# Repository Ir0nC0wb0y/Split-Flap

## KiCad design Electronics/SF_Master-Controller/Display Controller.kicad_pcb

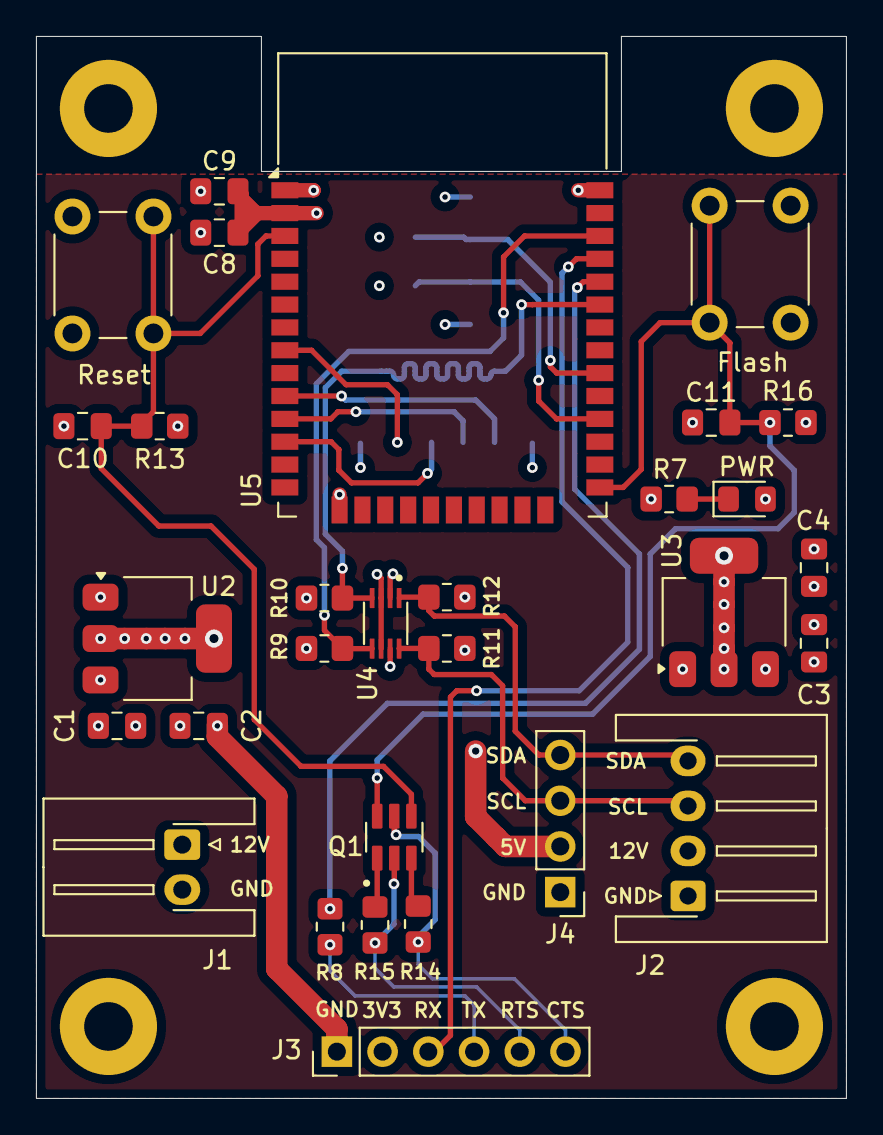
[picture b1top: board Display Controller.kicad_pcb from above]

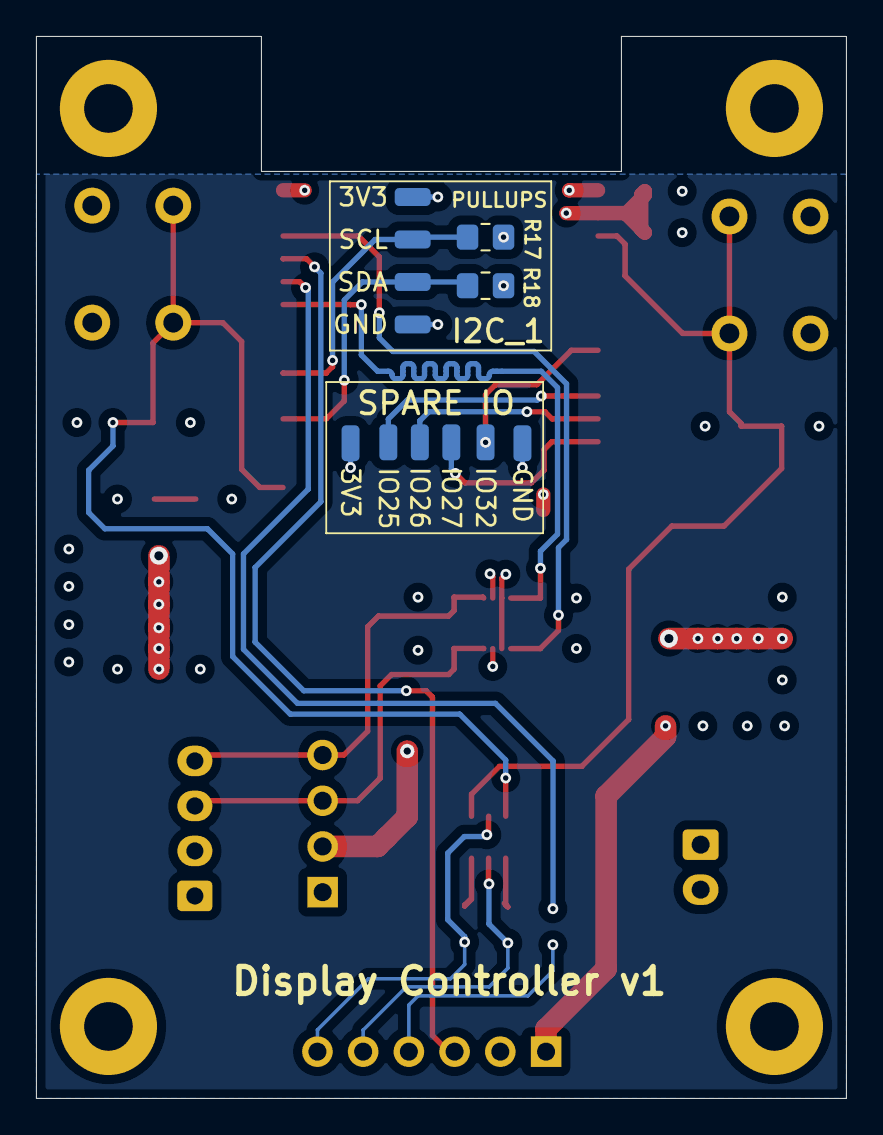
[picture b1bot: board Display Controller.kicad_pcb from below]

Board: 4 copper layers, 45.0 x 59.0 mm, 46 parts (12 on the bottom side), 24 nets.

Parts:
C1, C2, C3, C4: C; C_0805_2012Metric_Pad1.18x1.45mm_HandSolder
C8: 10uF; C_0805_2012Metric_Pad1.18x1.45mm_HandSolder
C9, C10, C11: 0.1uF; C_0805_2012Metric_Pad1.18x1.45mm_HandSolder
D1: LED; LED_0805_2012Metric_Pad1.15x1.40mm_HandSolder
H1, H2, H3, H4: MountingHole_Pad; MountingHole_2.7mm_M2.5_Pad
J1: Conn_01x02_Pin; JST_XH_S2B-XH-A-1_1x02_P2.50mm_Horizontal
J2: Conn_01x04_Pin; JST_XH_S4B-XH-A-1_1x04_P2.50mm_Horizontal
J3: Conn_01x06_Pin; PinHeader_1x06_P2.54mm_Vertical
J4: Conn_01x04_Pin; PinHeader_1x04_P2.54mm_Vertical
Q1: FMB2222A; SOT95P280X110-6N
R7: 150R; R_0805_2012Metric_Pad1.20x1.40mm_HandSolder
R8: 1k; R_0805_2012Metric_Pad1.20x1.40mm_HandSolder
R9, R10, R11, R12, R13, R14, R15, R16, R17, R18: 10k; R_0805_2012Metric_Pad1.20x1.40mm_HandSolder
SW3, SW4: SW_SPST; SW_PUSH_6mm_H4.3mm
TP1, TP2, TP3, TP4, TP5, TP6, TP7, TP8, TP9, TP10: TestPoint_Small; SolderWirePad_1x01_SMD_1x2mm
U2: LD1117S33TR_SOT223; SOT-223-3_TabPin2
U3: LD1117S50TR_SOT223; SOT-223-3_TabPin2
U4: TCA9406DCUR; SOP50P310X90-8N
U5: ESP32-WROOM-32E; ESP32-WROOM-32D

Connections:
+3V3: C2.1, C8.2, C9.2, J3.1, R9.1, R10.1, R13.1, R16.1, R17.1, R18.1, TP1.1, TP5.1, U2.2 (VO), U4.3 (VCCA), U4.6 (OE), U5.2 (VDD)
+5V: C4.1, D1.2 (A), J4.2, R11.1, R12.1, U3.2 (VO), U4.7 (VCCB)
+12V: C1.2, C3.2, J1.1, J2.2, U2.3 (VI), U3.3 (VI)
/ESP32/EN: C10.2, Q1.4, R13.2, SW3.2 (B), U5.3 (EN)
/ESP32/I2C_SCL_SPARE: R17.2, TP2.1, U5.30 (IO18)
/ESP32/I2C_SDA_SPARE: R18.2, TP3.1, U5.28 (IO17)
/ESP32/IO0: C11.2, Q1.6, R16.2, SW4.1 (A), U5.25 (IO0)
/ESP32/IO25: TP6.1, U5.10 (IO25)
/ESP32/IO26: TP7.1, U5.11 (IO26)
/ESP32/IO27: TP9.1, U5.12 (IO27)
/ESP32/IO32: TP10.1, U5.8 (IO32)
/I2C_SCL_5V: J2.3, J4.3, R11.2, U4.8 (SCL_B)
/I2C_SDA_5V: J2.4, J4.4, R12.2, U4.1 (SDA_B)
FTDI_CTS: J3.6, Q1.5, R14.1
FTDI_RTS: J3.5, Q1.2, R15.2
FTDI_RX: J3.3, U5.35 (TXD0/IO1)
FTDI_TX: R8.2, U5.34 (RXD0/IO3)
GND: C1.1, C2.2, C3.1, C4.2, C8.1, C9.1, C10.1, C11.1, J1.2, J2.1, J3.2, J4.1, R7.2, SW3.1 (A), SW4.2 (B), TP4.1, TP8.1, U2.1 (GND), U3.1 (GND), U4.2 (GND), U5.1 (GND), U5.15 (GND), U5.38 (GND)
I2C_SCL_3V3: R9.2, U4.5 (SCL_A), U5.36 (IO22)
I2C_SDA_3V3: R10.2, U4.4 (SDA_A), U5.33 (IO21)
unnamed: D1.1 (K), R7.1
unnamed: J3.4, R8.1
unnamed: Q1.1, R15.1
unnamed: Q1.3, R14.2

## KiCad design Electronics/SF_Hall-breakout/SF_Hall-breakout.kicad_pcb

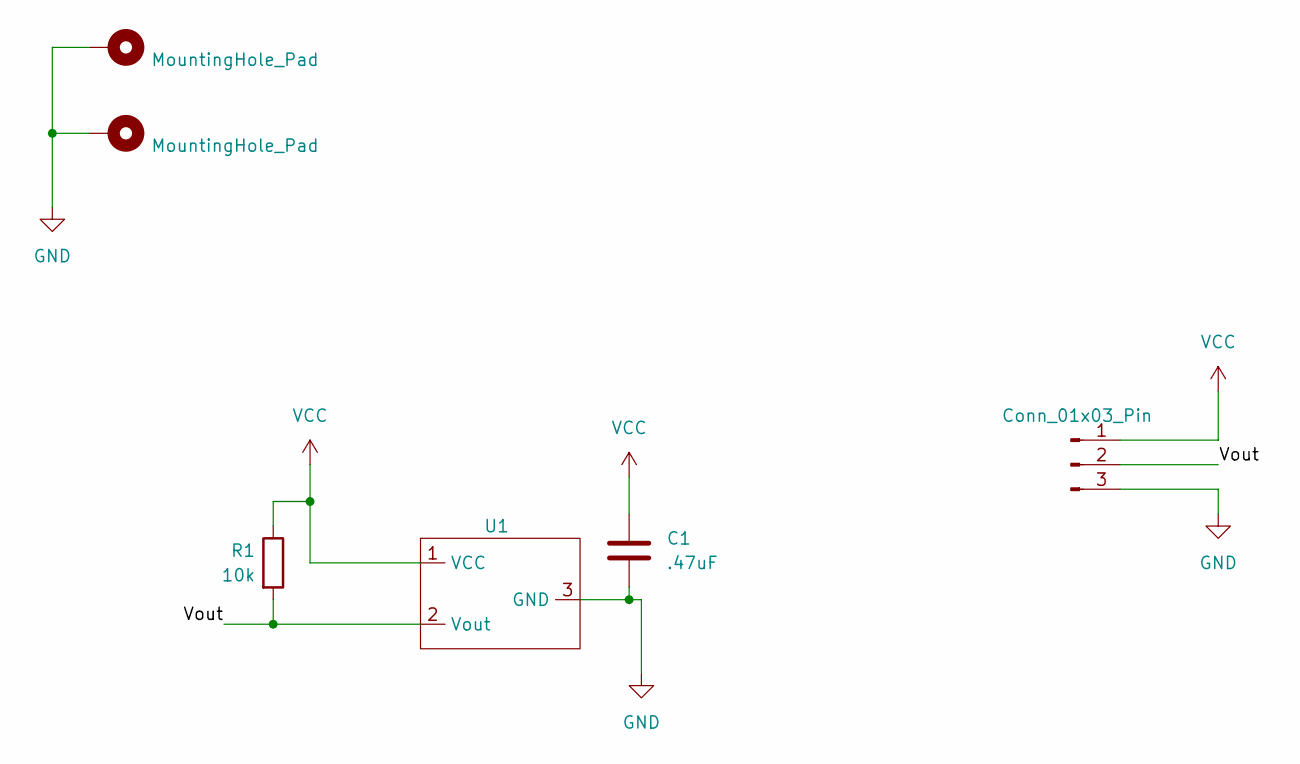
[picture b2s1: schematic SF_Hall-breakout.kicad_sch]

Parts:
C1: .47uF; C_0805_2012Metric_Pad1.18x1.45mm_HandSolder
H1, H2: MountingHole_Pad; MountingHole_2.2mm_M2_Pad
J1: Conn_01x03_Pin; PinHeader_1x03_P2.00mm_Vertical
R1: 10k; R_0805_2012Metric_Pad1.20x1.40mm_HandSolder
U1: SOT-23_Handsoldering

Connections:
/Vout: J1.2, R1.2, U1.2 (Vout)
GND: C1.2, H1.1, H2.1, J1.3, U1.3 (GND)
VCC: C1.1, J1.1, R1.1, U1.1 (VCC)

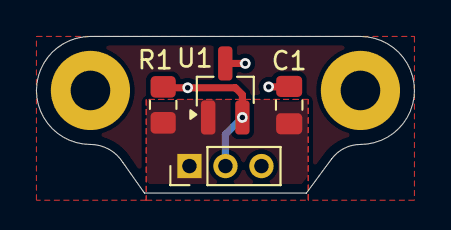
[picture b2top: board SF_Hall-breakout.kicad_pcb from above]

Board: 2 copper layers, 21.0 x 8.7 mm, 6 parts (0 on the bottom side), 3 nets.

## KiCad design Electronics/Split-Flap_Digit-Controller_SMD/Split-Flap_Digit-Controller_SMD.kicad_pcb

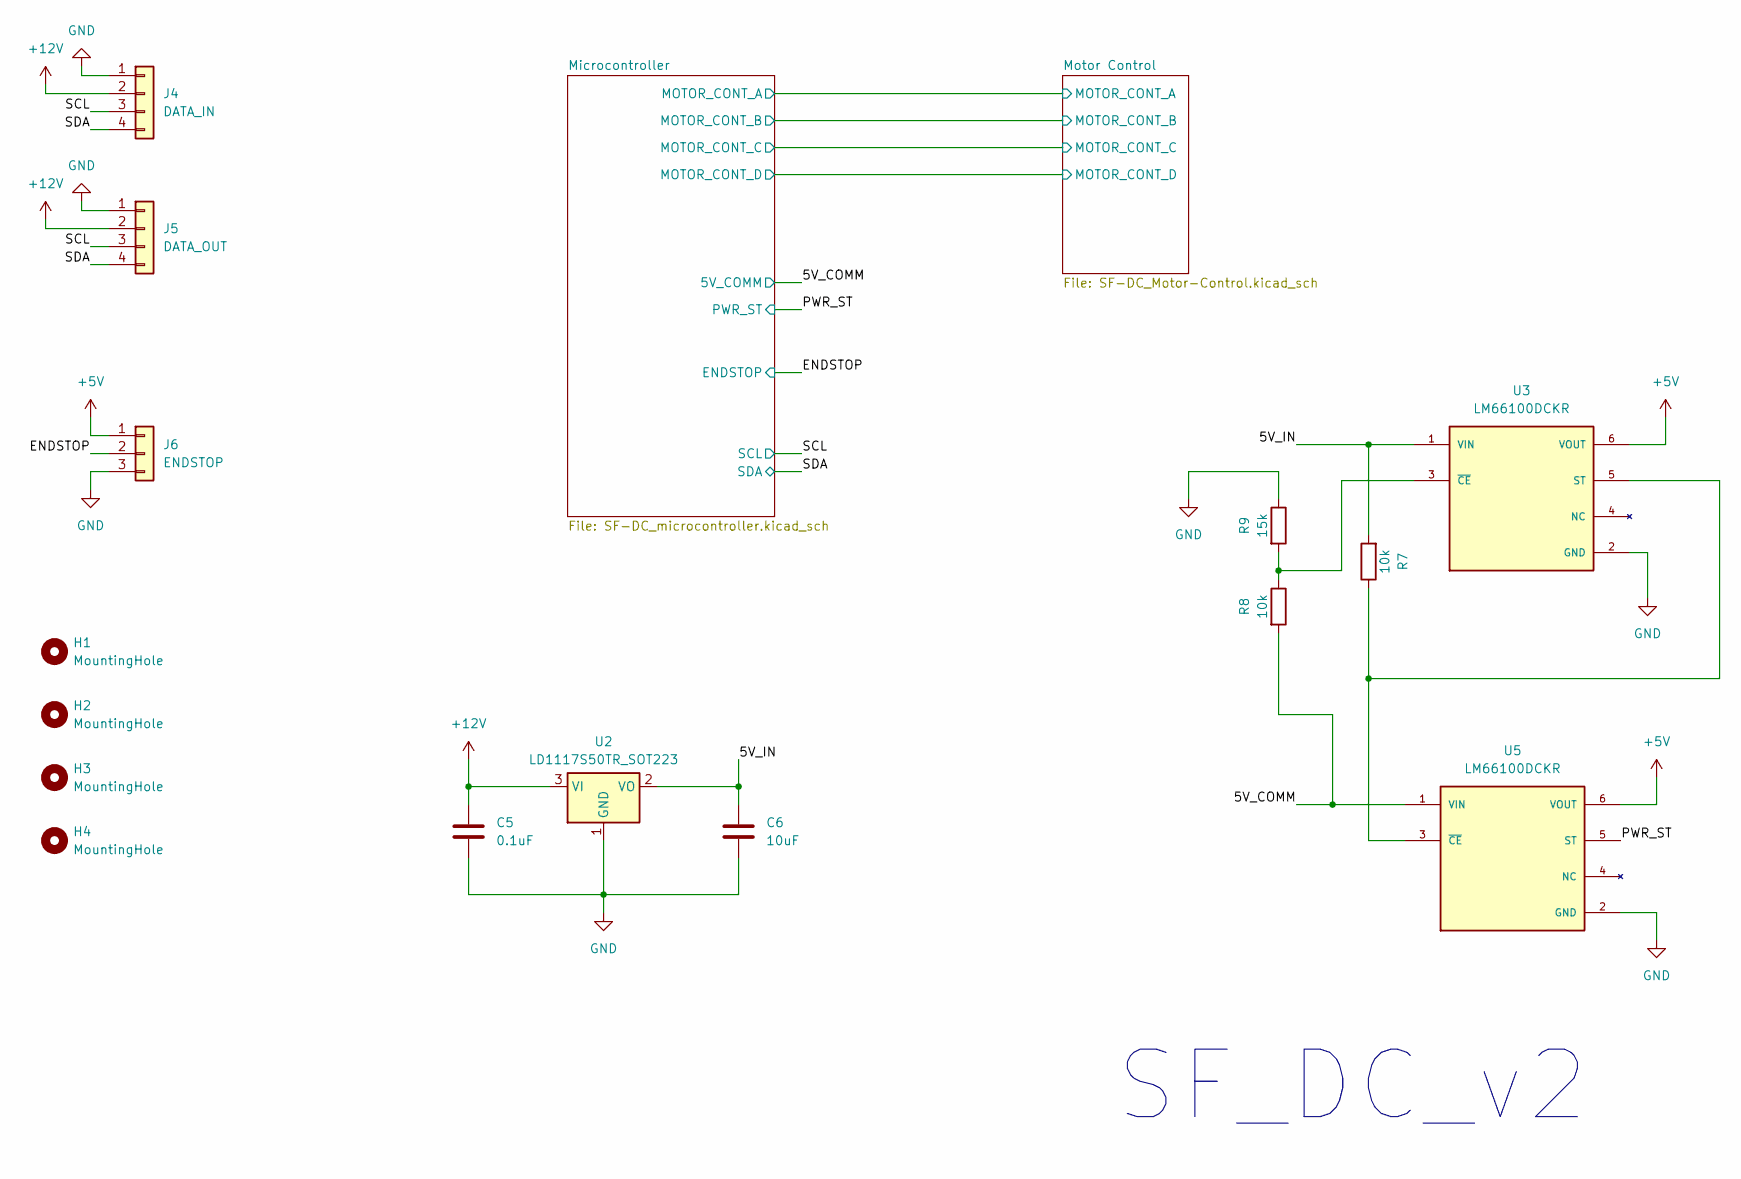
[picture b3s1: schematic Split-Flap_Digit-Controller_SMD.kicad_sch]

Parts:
C5: 0.1uF; LED_0805_2012Metric_Pad1.15x1.40mm_HandSolder
C6: 10uF; LED_0805_2012Metric_Pad1.15x1.40mm_HandSolder
H1, H2, H3, H4: MountingHole; MountingHole_2.7mm_M2.5_DIN965_Pad_TopBottom
J4: DATA_IN; JST_XH_S4B-XH-A-1_1x04_P2.50mm_Horizontal
J5: DATA_OUT; JST_XH_S4B-XH-A-1_1x04_P2.50mm_Horizontal
J6: ENDSTOP; JST_XH_S3B-XH-A-1_1x03_P2.50mm_Horizontal
R7, R8: 10k; R_0805_2012Metric_Pad1.20x1.40mm_HandSolder
R9: 15k; R_0805_2012Metric_Pad1.20x1.40mm_HandSolder
U2: LD1117S50TR_SOT223; SOT-223-3_TabPin2
U3, U5: LM66100DCKR; SOT65P210X110-6N; PARTREV Rev. A

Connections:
+5V: J6.1, U3.6 (VOUT), U5.6 (VOUT); also elsewhere on the board
+12V: C5.1, J4.2, J5.2, U2.3 (VI); also elsewhere on the board
/5V_COMM: R8.2, U5.1 (VIN); also elsewhere on the board
/5V_IN: C6.1, R7.2, U2.2 (VO), U3.1 (VIN)
/ENDSTOP: J6.2; also elsewhere on the board
/PWR_ST: U5.5 (ST); also elsewhere on the board
/SCL: J4.3, J5.3; also elsewhere on the board
/SDA: J4.4, J5.4; also elsewhere on the board
GND: C5.2, C6.2, J4.1, J5.1, J6.3, R9.1, U2.1 (GND), U3.2 (GND), U5.2 (GND); also elsewhere on the board
unnamed: R7.1, U3.5 (ST), U5.3 (~CE)
unnamed: R8.1, R9.2, U3.3 (~CE)

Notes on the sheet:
SF_DC_v2

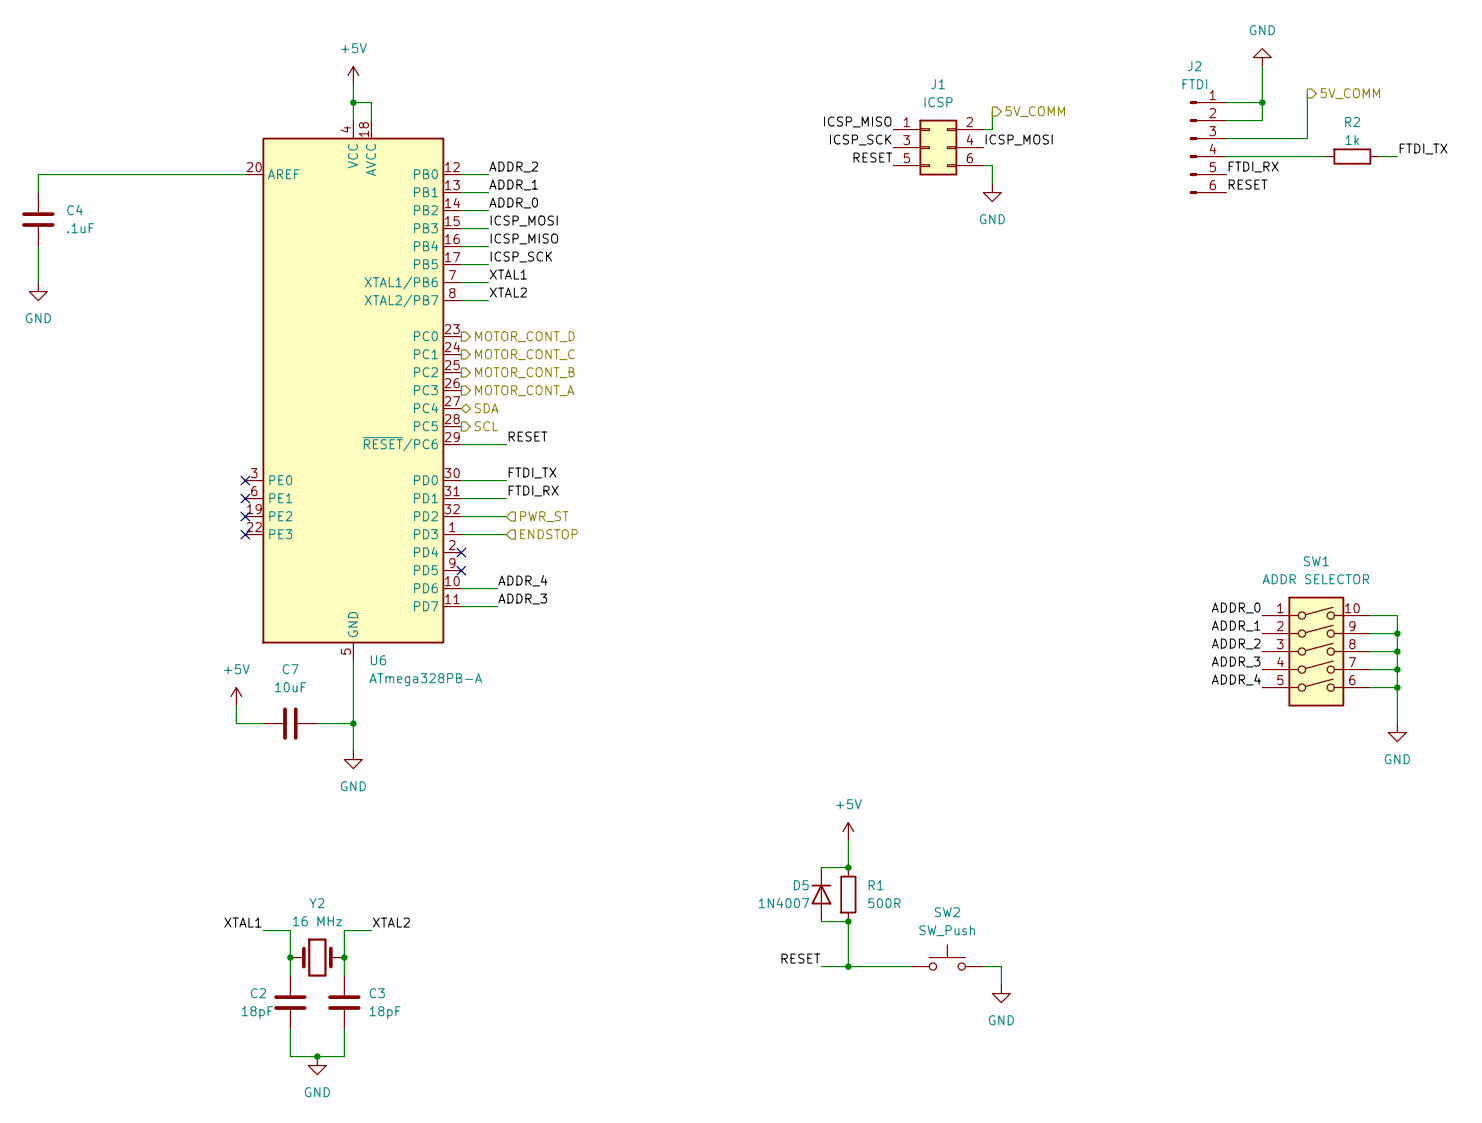
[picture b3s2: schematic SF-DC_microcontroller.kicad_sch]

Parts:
C2: 18pF; C_0805_2012Metric_Pad1.18x1.45mm_HandSolder; Part Number FG28C0G1H180JNT06
C3: 18pF; C_0805_2012Metric_Pad1.18x1.45mm_HandSolder; part_no FG28C0G1H180JNT06
C4: .1uF; C_0805_2012Metric_Pad1.18x1.45mm_HandSolder
C7: 10uF; C_0805_2012Metric_Pad1.18x1.45mm_HandSolder
D5: 1N4007; D_SMA_Handsoldering
J1: ICSP; PinHeader_2x03_P2.54mm_Vertical
J2: FTDI; PinHeader_1x06_P2.54mm_Vertical
R1: 500R; R_0805_2012Metric_Pad1.20x1.40mm_HandSolder
R2: 1k; R_0805_2012Metric_Pad1.20x1.40mm_HandSolder
SW1: ADDR SELECTOR; SW_DIP_SPSTx05_Slide_6.7x14.26mm_W7.62mm_P2.54mm_LowProfile
SW2: SW_Push; SW_PUSH_6mm
U6: ATmega328PB-A; TQFP-32_7x7mm_P0.8mm
Y2: 16 MHz; Crystal_SMD_0603-2Pin_6.0x3.5mm_HandSoldering

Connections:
+5V: C7.2, D5.1 (K), R1.1, U6.4 (VCC), U6.18 (AVCC); also elsewhere on the board
/5V_COMM: J1.2, J2.3; also elsewhere on the board
/ENDSTOP: U6.1 (PD3); also elsewhere on the board
/Microcontroller/ADDR_0: SW1.1, U6.14 (PB2)
/Microcontroller/ADDR_1: SW1.2, U6.13 (PB1)
/Microcontroller/ADDR_2: SW1.3, U6.12 (PB0)
/Microcontroller/ADDR_3: SW1.4, U6.11 (PD7)
/Microcontroller/ADDR_4: SW1.5, U6.10 (PD6)
/Microcontroller/FTDI_RX: J2.5, U6.31 (PD1)
/Microcontroller/FTDI_TX: R2.1, U6.30 (PD0)
/Microcontroller/ICSP_MISO: J1.1, U6.16 (PB4)
/Microcontroller/ICSP_MOSI: J1.4, U6.15 (PB3)
/Microcontroller/ICSP_SCK: J1.3, U6.17 (PB5)
/Microcontroller/MOTOR_CONT_A: U6.26 (PC3); also elsewhere on the board
/Microcontroller/MOTOR_CONT_B: U6.25 (PC2); also elsewhere on the board
/Microcontroller/MOTOR_CONT_C: U6.24 (PC1); also elsewhere on the board
/Microcontroller/MOTOR_CONT_D: U6.23 (PC0); also elsewhere on the board
/Microcontroller/RESET: D5.2 (A), J1.5, J2.6, R1.2, SW2.1, U6.29 (~RESET/PC6)
/Microcontroller/XTAL1: C2.2, U6.7 (XTAL1/PB6), Y2.1
/Microcontroller/XTAL2: C3.2, U6.8 (XTAL2/PB7), Y2.2
/PWR_ST: U6.32 (PD2); also elsewhere on the board
/SCL: U6.28 (PC5); also elsewhere on the board
/SDA: U6.27 (PC4); also elsewhere on the board
GND: C2.1, C3.1, C4.2, C7.1, J1.6, J2.1, J2.2, SW1.6, SW1.7, SW1.8, SW1.9, SW1.10, SW2.2, U6.5 (GND), U6.21 (GND); also elsewhere on the board
unnamed: J2.4, R2.2
unnamed: C4.1, U6.20 (AREF)

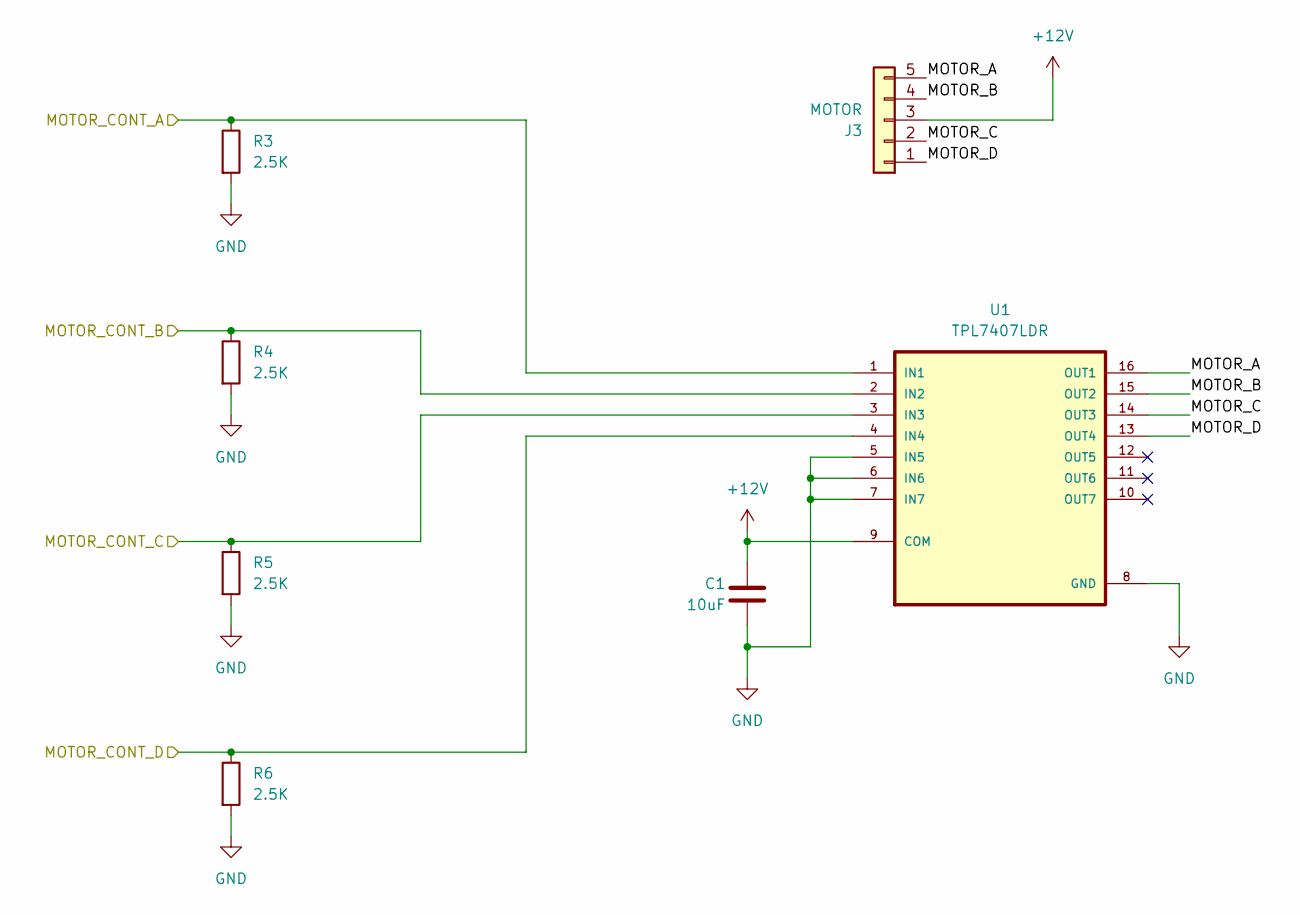
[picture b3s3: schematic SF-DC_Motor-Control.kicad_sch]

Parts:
C1: 10uF; R_0805_2012Metric_Pad1.20x1.40mm_HandSolder
J3: MOTOR; JST_XH_S5B-XH-A-1_1x05_P2.50mm_Horizontal
R3, R4, R5, R6: 2.5K; R_0805_2012Metric_Pad1.20x1.40mm_HandSolder
U1: TPL7407LDR; SOIC127P600X175-16N

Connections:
+12V: C1.2, J3.3, U1.9 (COM); also elsewhere on the board
/Microcontroller/MOTOR_CONT_A: R3.1, U1.1 (IN1); also elsewhere on the board
/Microcontroller/MOTOR_CONT_B: R4.1, U1.2 (IN2); also elsewhere on the board
/Microcontroller/MOTOR_CONT_C: R5.1, U1.3 (IN3); also elsewhere on the board
/Microcontroller/MOTOR_CONT_D: R6.1, U1.4 (IN4); also elsewhere on the board
/Motor Control/MOTOR_A: J3.5, U1.16 (OUT1)
/Motor Control/MOTOR_B: J3.4, U1.15 (OUT2)
/Motor Control/MOTOR_C: J3.2, U1.14 (OUT3)
/Motor Control/MOTOR_D: J3.1, U1.13 (OUT4)
GND: C1.1, R3.2, R4.2, R5.2, R6.2, U1.5 (IN5), U1.6 (IN6), U1.7 (IN7), U1.8 (GND); also elsewhere on the board

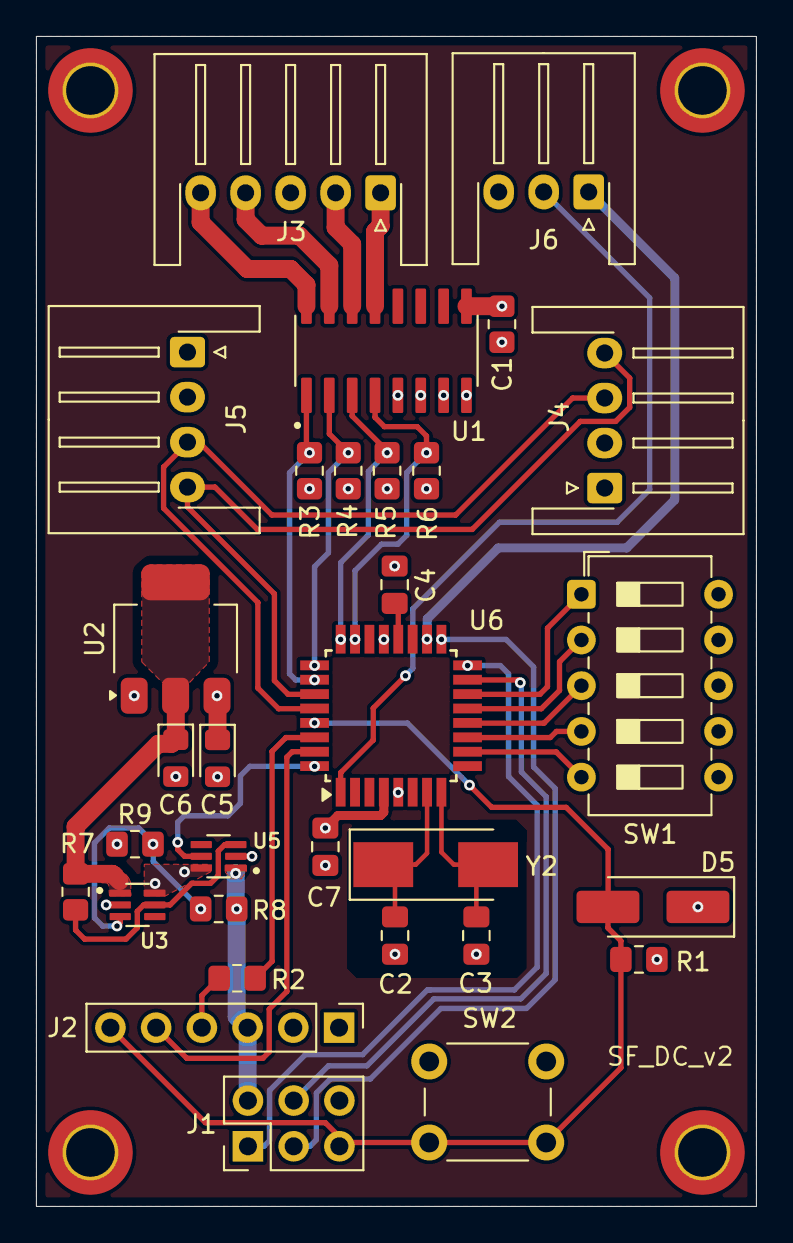
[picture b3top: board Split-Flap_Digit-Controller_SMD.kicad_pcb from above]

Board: 4 copper layers, 40.0 x 65.0 mm, 35 parts (0 on the bottom side), 34 nets.

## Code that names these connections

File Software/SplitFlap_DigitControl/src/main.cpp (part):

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// Stepper lib expects: blue-yellow, pink-orange


#define PIN_MOTOR_A 17  // yellow
#define PIN_MOTOR_B 16  // orange
#define PIN_MOTOR_C 15  // pink
#define PIN_MOTOR_D 14  // blue
#define PIN_ENDSTOP  3
#define PIN_ADDR_0  10
#define PIN_ADDR_1   9
#define PIN_ADDR_2   8
#define PIN_ADDR_3   7
#define PIN_ADDR_4   6

// I2C Setup
  void i2c_receiveEvent(int numBytesReceived);
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// Motor Setup
  #define HALFSTEP 8
  #define FULLSTEP 4
  AccelStepper stepper1(HALFSTEP, PIN_MOTOR_B, PIN_MOTOR_C, PIN_MOTOR_D, PIN_MOTOR_A);
  #define MOTOR_SPEED_HOMING   300.0
  #define MOTOR_SPEED_RUN     1500.0
  #define MOTOR_ACCEL         3000.0
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
  // Calculate I2C Address
  // Address Pins
    pinMode(PIN_ADDR_0, INPUT_PULLUP);
    pinMode(PIN_ADDR_1, INPUT_PULLUP);
    pinMode(PIN_ADDR_2, INPUT_PULLUP);
    pinMode(PIN_ADDR_3, INPUT_PULLUP);
    pinMode(PIN_ADDR_4, INPUT_PULLUP);
  i2c_address = Address_Calc();
  Serial.print("Starting I2C bus with address: "); Serial.println(i2c_address);
  // Start I2C bus with address
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  Wire.onRequest(I2C_requestEvent);

  // Set up pins
    //pinMode(PIN_MOTOR_A, OUTPUT);
    //pinMode(PIN_MOTOR_C, OUTPUT);
    //pinMode(PIN_MOTOR_B, OUTPUT);
    //pinMode(PIN_MOTOR_D, OUTPUT);

    // Endstop, also needs to become an interrupt
    pinMode(PIN_ENDSTOP, INPUT_PULLUP);
    attachInterrupt(digitalPinToInterrupt(PIN_ENDSTOP), Endstop_Interrupt, FALLING);

    
    
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}

int Address_Calc() {
  bool bit0 = digitalRead(PIN_ADDR_0);
  bool bit1 = digitalRead(PIN_ADDR_1);
  bool bit2 = digitalRead(PIN_ADDR_2);
  bool bit3 = digitalRead(PIN_ADDR_3);
  bool bit4 = digitalRead(PIN_ADDR_4);

  Serial.print("Address bits: ");
    Serial.print(bit4);
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}

void Endstop_Calibrate() {
  bool pin_state = digitalRead(PIN_ENDSTOP);
  // Routine to calibrate offset

  if (motor_turns >= 0) {
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  Serial.print("Current SR value: ");
    Serial.println(motor_sr.getValue());

  attachInterrupt(digitalPinToInterrupt(PIN_ENDSTOP), Endstop_Calibrate, CHANGE);

  // Gather rotation data
  stepper1.setSpeed(MOTOR_CALIBRATE_SPEED);
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  }

  // Return to regular endstop behavior
  attachInterrupt(digitalPinToInterrupt(PIN_ENDSTOP), Endstop_Interrupt, FALLING);
  cross_endstop = 0;
  motor_turns = 0;
  // Home Motor
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
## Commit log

2025-05-09 Initial Release
2025-05-09 Demo cycles then random
2025-05-18 Added calibrate routine separate from demo
2025-05-19 Fixed Positioning Calculations
    All methodology now the same
2025-06-05 Added simple I2C comms and upgrade calibration
    New calibration routine takes position of pre and post endstop crossing and averages
2025-06-07 Created SF_Master program
2025-06-07 master pushes new position to digit.
    Very simple single direction communication
2025-06-14 Added Master Controller design and cleanup naming
2025-07-03 Update for production microcontroller (esp32)
2025-07-05 Updates for regressions
2025-07-11 feat(SF_Master): website splash page
2025-07-12 feat(SF_Master): website display and set
2025-07-13 style(SF_Master): samle page to build out flap animation
2025-07-13 style(SF_Master): and now styled
2025-07-14 style(SF_Master): simpler controls more controlled by styling, only change characters and when animated
2025-07-14 feat(SF_Master): animated flaps in display page preview
2025-07-14 fix(SF_Master): list the allowed characters
2025-07-16 refactor(SF_Master): more consistent styling
2025-07-16 fix(SF_Master): independent preview character updates
2025-07-16 feat(SF_Master): fetch data, implement server (by Copilot) based off of openapi.yaml
2025-07-21 I2C handling of multiple digits
2025-07-22 fix(SF_Master): proper location for FS files
2025-07-22 fix(SF_Master): use LittleFS instead of SPIFFS
2025-07-25 Updates for debug, compiled, flashed, tested
2025-07-26 Removed delay from loop
    all timing shall be non-blocking
2025-07-26 Searches through WiFi directory for matching SSID/conf files
2025-07-27 Debugged connection
2025-07-27 Added create AP if STA doesn't connect
2025-07-31 Adding in display functions
2025-08-01 Refactored code into files
2025-08-02 User config options available in main, all else are "restricted" to lower levels
2025-08-02 Added countdown, flashed
    Still have an issue of the unit not displaying (remains null character)
2025-08-02 Converted to String from char[]
2025-08-02 Removed old char[] references
2025-08-03 updated time function and added date function, added universal alignment function
2025-08-03 extended unit testing, particularly for number of digits
2025-08-03 Improve display and I2C debug logging and timing
    Added detailed Serial output to send_String for better visibility of message sending. Refactored send_character to use a non-blocking wait loop with a configurable DIGIT_READY_WAIT interval. Introduc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
2025-08-03 Fix missing newline in send_String completion log
    Changed Serial.print to Serial.println for the 'ms' suffix in send_String, ensuring the completion message is properly terminated with a newline.
2025-08-04 Refactor display, time, and WiFi handlers to return status
    Updated HandleDisplay, handle_time, and checkWiFi to return a boolean indicating if they performed an action. Added timing and status reporting in main loop for performance diagnostics. Improved disp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
2025-08-04 Refactor display, webserver, and timing logic
    Improved frame selection logic in HandleDisplay by using a temporary variable for next frame calculation. Updated I2C debug delay for more realistic testing. Webserver now syncs display_string and us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
2025-08-04 Optimize display string updates and update comments
    Added a check in send_String to only send characters that differ from the current display, reducing unnecessary transmissions. Updated comments in main.cpp to clarify the time format for countdown_ev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
2025-08-09 Refactor display and countdown variable organization
    Grouped related display and countdown variables for improved code clarity in main.cpp. Added message parsing logic and frame handling refinements in functions_display.cpp to support message chunking 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
2025-08-09 Add display message string and refactor config
    Introduced a new variable for display messages and reorganized configuration variables for clarity. Added a placeholder for pushing new strings to the server after display updates.
